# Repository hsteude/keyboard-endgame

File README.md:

# Let's create a custom keyboard

## Requirements

1. Planck layout
2. Ultra portable (low profile)
3. Wireless
4. Case

## Idas / Steps

1. Build layout using [ergogen](https://ergogen.xyz/)
2. PCB routing using [Kicad](https://www.kicad.org/)?
3. Create Firmware using [ZMK](https://zmk.dev/docs)
4. Case design also with ergogen?

## Open queistions

1. What kind of microcontroler do I need?
  - According to [this](https://golem.hu/guide/keyboard-matrix/) arcticle, A
    controller for the planck keyboard needs at least 16 pins.
  - ZMK seems to support Nice! Hardware. (e.g. the Nice!60 Board)
2. Are there footprints for the Nice!Nano for both ergogen and Kicad?
  - At least according to [this](https://www.reddit.com/r/ErgoMechKeyboards/comments/sluweg/pro_micro_vs_nce_nano/), the nice can be used with the same footprints.
2. How exactly does the ergogen tools work?
  - [This guy](https://github.com/cacheworks/Plank) already configured a PCB layout for the Planck. However, as far as I can tell it neither supports hotswapaable switches nor a case.
3. Can the controller (and battery) be placed under the keys?
  - Working on it

## Next steps:
- [x] Choose Controller
  - The [Nice!Nano](https://nicekeyboards.com/docs/nice-nano/pinout-schematic)
  seems to meet my requirements.
- [ ] Create ergogen files
  - Currently working on this
- [ ] Order PCB
- [ ] Create parts list for prototype
- [ ] Brainstorm ideas for a slim case

## Hardware
- Nice!Nano
  [controller](https://splitkb.com/collections/keyboard-parts/products/nice-nano)
  (ca 35 EUR)
- [Battery](https://www.ebay.co.uk/itm/195234783901) that fits between the
  controller pins (ca 15 EUR).
- Switches, keycaps, hotswap sockets ...

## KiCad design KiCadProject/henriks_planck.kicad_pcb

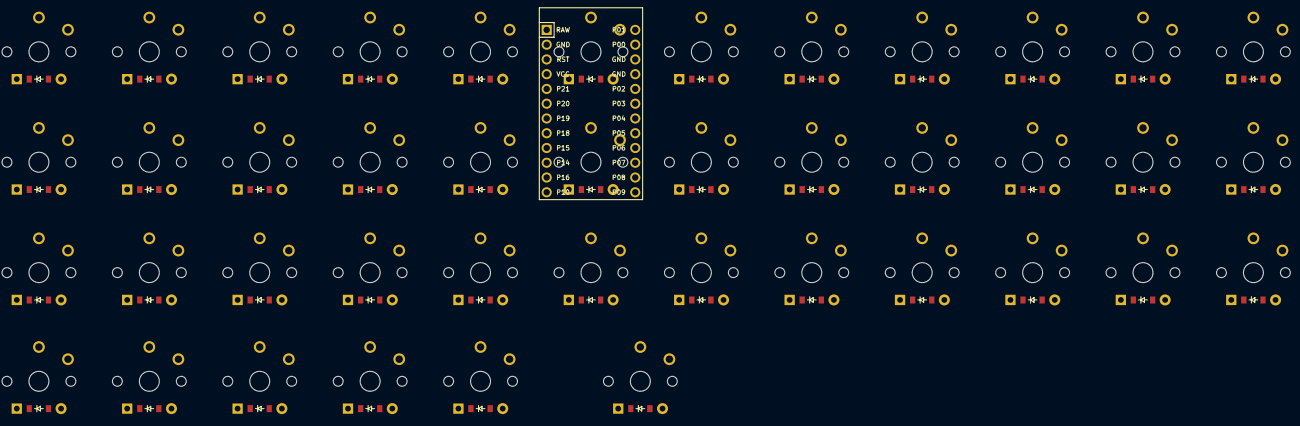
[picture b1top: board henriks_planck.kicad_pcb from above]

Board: 2 copper layers, 85 parts (0 on the bottom side), 16 nets, no tracks yet.

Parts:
D1, D2, D3, D4, D5, D6, D7, D8, D9, D10, D11, D12, D13, D14, D15, D16, D17, D18, D19, D20, D21, D22, D23, D24, D25, D26, D27, D28, D29, D30, D31, D32, D33, D34, D35, D36, D37, D38, D39, D40, D41, D42: ComboDiode
MCU1: ProMicro
S1, S2, S3, S4, S5, S6, S7, S8, S9, S10, S11, S12, S13, S14, S15, S16, S17, S18, S19, S20, S21, S22, S23, S24, S25, S26, S27, S28, S29, S30, S31, S32, S33, S34, S35, S36, S37, S38, S39, S40, S41, S42: PG1350

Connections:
GND: MCU1.2, MCU1.15, MCU1.16
P4: D1.1, D1.2, D2.1, D2.2, D3.1, D3.2, D37.1, D37.2, MCU1.19, S1.2, S2.2, S3.2, S37.2
P5: D4.1, D4.2, D5.1, D5.2, D6.1, D6.2, D38.1, D38.2, MCU1.20, S4.2, S5.2, S6.2, S38.2
P6: D7.1, D7.2, D8.1, D8.2, D9.1, D9.2, D39.1, D39.2, MCU1.21, S7.2, S8.2, S9.2, S39.2
P7: D10.1, D10.2, D11.1, D11.2, D12.1, D12.2, D40.1, D40.2, MCU1.22, S10.2, S11.2, S12.2, S40.2
P8: D13.1, D13.2, D14.1, D14.2, D15.1, D15.2, D41.1, D41.2, D42.1, D42.2, MCU1.23, S13.2, S14.2, S15.2, S41.2, S42.2
P9: D16.1, D16.2, D17.1, D17.2, D18.1, D18.2, MCU1.24, S16.2, S17.2, S18.2
P10: D19.1, D19.2, D20.1, D20.2, D21.1, D21.2, MCU1.12, S19.2, S20.2, S21.2
P11: D22.1, D22.2, D23.1, D23.2, D24.1, D24.2, S22.2, S23.2, S24.2
P12: D25.1, D25.2, D26.1, D26.2, D27.1, D27.2, S25.2, S26.2, S27.2
P13: D28.1, D28.2, D29.1, D29.2, D30.1, D30.2, S28.2, S29.2, S30.2
P14: D31.1, D31.2, D32.1, D32.2, D33.1, D33.2, D34.1, D34.2, D35.1, D35.2, D36.1, D36.2, MCU1.10, S31.2, S32.2, S33.2, S34.2, S35.2, S36.2
P16: D37.1, D37.2, D38.1, D38.2, D39.1, D39.2, D40.1, D40.2, D41.1, D41.2, D42.1, D42.2, MCU1.11, S37.1, S38.1, S39.1, S40.1, S41.1, S42.1
P19: D3.1, D3.2, D6.1, D6.2, D9.1, D9.2, D12.1, D12.2, D15.1, D15.2, D18.1, D18.2, D21.1, D21.2, D24.1, D24.2, D27.1, D27.2, D30.1, D30.2, D33.1, D33.2, D36.1, D36.2, MCU1.7, S3.1, S6.1, S9.1, S12.1, S15.1, S18.1, S21.1, S24.1, S27.1, S30.1, S33.1, S36.1
P20: D2.1, D2.2, D5.1, D5.2, D8.1, D8.2, D11.1, D11.2, D14.1, D14.2, D17.1, D17.2, D20.1, D20.2, D23.1, D23.2, D26.1, D26.2, D29.1, D29.2, D32.1, D32.2, D35.1, D35.2, MCU1.6, S2.1, S5.1, S8.1, S11.1, S14.1, S17.1, S20.1, S23.1, S26.1, S29.1, S32.1, S35.1
P21: D1.1, D1.2, D4.1, D4.2, D7.1, D7.2, D10.1, D10.2, D13.1, D13.2, D16.1, D16.2, D19.1, D19.2, D22.1, D22.2, D25.1, D25.2, D28.1, D28.2, D31.1, D31.2, D34.1, D34.2, MCU1.5, S1.1, S4.1, S7.1, S10.1, S13.1, S16.1, S19.1, S22.1, S25.1, S28.1, S31.1, S34.1

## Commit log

2023-01-09 Git repo reorga
